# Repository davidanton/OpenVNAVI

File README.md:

# OpenVNAVI

**Bachelor Thesis at the Media Computing Group, Computer Science Department @ RWTH Aachen University (Germany)**
**Author:** [David Antón Sánchez](https://hci.rwth-aachen.de/sanchez)
**Project Website:** https://hci.rwth-aachen.de/openvnavi

---
#Wiki

- [Home](https://github.com/davidanton/OpenVNAVI/wiki)

- [Setting Up the Raspberry Pi 2](https://github.com/davidanton/OpenVNAVI/wiki/Setting-Up-the-Raspberry-Pi-2)

---

###System Description

OpenVNAVI is a vest equipped with a depth sensor and array of vibration motor units that allow people with visual impairment to avoid obstacles in the environment.

The ASUS Xtion PRO LIVE depth sensor, positioned onto the user’s chest scans the environment as the user moves. From the video feed of the depth sensor a frame is captured and then processed by the Raspberry Pi 2. Each frame is downsampled from 640x480 to 16x8 and each pixel is then mapped to a vibration motor unit forming an array positioned onto the user’s belly.

The grayscale value of each pixel on the lower resolution frame is assigned to a PWM voltage value generated by the Raspberry Pi 2 via PWM drivers that will drive each vibration motor obtaining a vibration amplitude value as a function of the proximity of an object.

With this method the vibration motor unit array is able to represent a vibratory image onto the user’s belly to help create a mental representation of the obstacles in the scene.

---

###Pictures

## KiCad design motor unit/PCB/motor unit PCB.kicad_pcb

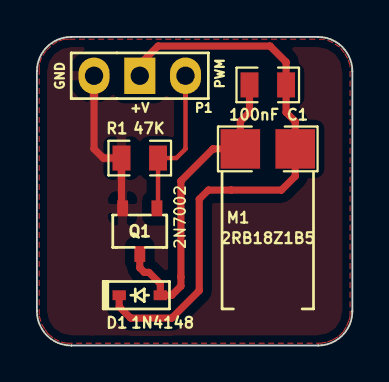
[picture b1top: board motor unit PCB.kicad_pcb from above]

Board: 2 copper layers, 17.5 x 17.1 mm, 6 parts (0 on the bottom side), 4 nets.

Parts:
C1: 100nF; SMD0805
D1: 1N4148; SOD-323
M1: 2RB18Z1B5; Vibration_motor
P1: CONN; Pin_Header_Straight_1x03_MOD
Q1: 2N7002; SOT23-5_MOD_PINOUT
R1: 47K; SMD0805

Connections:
+5V: C1.1, D1.1, M1.1, P1.2
GND: P1.1, Q1.3, R1.2
unnamed: C1.2, D1.2, M1.2, Q1.1
unnamed: P1.3, Q1.2, R1.1

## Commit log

2015-06-04 Added Motor Unit PCB and KiCAD libraries
2015-06-04 Add Motor Unit FreeCAD 3D files
2015-06-04 Fix KiCAD libraries folder
2015-06-05 Add final motor unit PCB gerbers
2015-06-10 Update motor unit 3D files
2015-06-10 Update motor unit PCB files
2015-06-10 Update motor unit 3D
2015-06-10 Update motor unit 3D and PCB
2015-06-13 Update motor unit PCB
2015-06-16 Fix motor unit PCB
2015-07-04 Fix Motor Unit 3D cable opening size
2015-07-09 Add Raspberry Pi 2 python code
2015-07-09 First usable version
2015-07-10 Add start/stop & beep
2015-07-10 Code cleanup
2015-07-10 Add strobe vibration function, code cleanup
2015-07-10 Code cleanup, tabs to spaces
2015-07-10 Enable KeyboardInterrupt during initialization
2015-07-10 Minor changes
2015-07-11 Add gitignore, minor code cleanup
2015-07-14 Fix silkscreen placement
2015-07-20 Cleanup
2015-07-20 Add datasheets
2015-07-20 Add sensor specs files
2015-07-20 Add driver PCB
2015-07-20 Add 3D enclosure, sensor support and washers
2015-08-15 Fix PWM not set when sensor data = 0, update driver unit and motor unit
2015-08-15 Web server for setting vibration motor levels
2015-08-16 Fix black border removed from frame640, providing better downsampling results
2015-08-16 Add distance detection threshold to reduce the vibration noise of distant objects, minor cleanup
2015-08-17 Added PNG input
2015-08-17 PNG pattern example file
2015-08-17 find & replace
2015-08-17 Fix: Make the vest run with Kinect by default (even not set from the web server side)
2015-08-17 Fix initialization not performed in main function
2015-08-18 added web server and multiprocessing
2015-08-18 Add modifications by chatchavan
2015-08-18 Replaced benchmarking code to avoid misleading results
2015-08-18 Simplifying condition in switch states.
2015-08-18 Disable benchmark
2015-08-18 Add missing files for the web server
2015-08-18 Fix conflict
2015-08-18 Add changes by chatchavan, resolved conflict
2015-08-18 Refactor PWM mapping to ease transitioning controls to web.
2015-08-18 clean up message handling from web server
2015-08-18 Allow retrieving depth and PWM values from the web.
2015-08-18 fix bug that prevents PWM setting from web server
2015-09-07 Update README, add PDF schematics
2015-09-07 Add Bachelor Thesis Document and images
2015-09-07 Fix image
2015-09-08 1.0 Bachelor Thesis version with documentation
2015-09-08 Add images, update README
2015-09-08 Update images
2015-10-14 Rename Bachelor Thesis file
